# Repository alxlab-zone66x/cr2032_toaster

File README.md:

# CR2032 Toaster

This is intended to slot in vertically into a 1/2AA battery holder seen on many Macintosh computers for the PRAM battery. It will allow the use of the less expensive, easier to find and less leaky CR2032 coin batteries.

This is meant to be used laying flat in the battery holder like so:

There's also two extra through holes to solder wires for other uses.

## Bill of Materials

### v1.0 to v1.3

| Quantity | Product Number  | Datasheet                                                    |
| :------- | --------------- | ------------------------------------------------------------ |
| 1        | BAT-HLD-001-THM | [datasheet](datasheets/BAT-HLD-001-THM_Linx_Technologies.pdf) |

### v1.3b

| Quantity | Product Number  | Datasheet                                      |
| :------- | --------------- | ---------------------------------------------- |
| 1        | BAT-HLD-005-THM | [datasheet](datasheets/BAT-HLD-005-THM_TE.pdf) |

### v1.3c

| Quantity | Product Number | Datasheet                                                    |
| :------- | -------------- | ------------------------------------------------------------ |
| 1        | RK-2014        | [datasheet](datasheets/Reekart_RK-2014_1.png), [datasheet](datasheets/Reekart_RK-2014_2.png) |

### v1.3d

| Quantity | Product Number | Datasheet                                     |
| :------- | -------------- | --------------------------------------------- |
| 1        | MY-2032-08L    | [datasheet](datasheets/MYOUNG_MY-2032-08.pdf) |

## Manufacturing

The gerber, bom and component placement files are in the production folder.

The release includes the manufacturing files for JLCPCB specifically. If you need to the gerber files, BOM or component pick & place in a different format then you would have to generate them yourself.

The PCB thickness chosen should be at least 1.6mm to provide good contact with the battery holder.

## License

CR2032 Toaster by [Alexandre Marcoux](https://github.com/alxlab-zone66x/cr2032_toaster) licensed under a <a rel="license" href="http://creativecommons.org/licenses/by-nc-sa/4.0/">Creative Commons Attribution-NonCommercial-ShareAlike 4.0 International License</a>.

## Community

For more great retro hardware projects and a great community check out:

Join us in #skunkworks on [Discord](https://discord.gg/GKcvtgU7P9) to help make retro solutions available to all.

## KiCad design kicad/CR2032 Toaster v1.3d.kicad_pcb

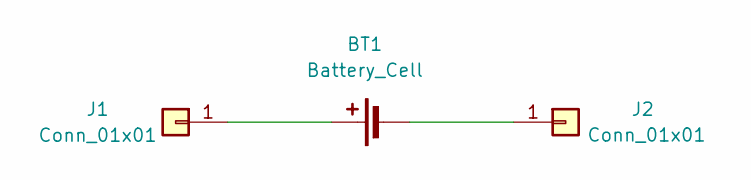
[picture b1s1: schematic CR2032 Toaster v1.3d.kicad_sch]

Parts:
BT1: Battery_Cell; BatteryHolder_MYOUNG_MY-2032-08_1x2032; LCSC C19184096
J1, J2: Conn_01x01; 6mm PTS

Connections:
unnamed: BT1.1 (+), J1.1
unnamed: BT1.2 (-), J2.1

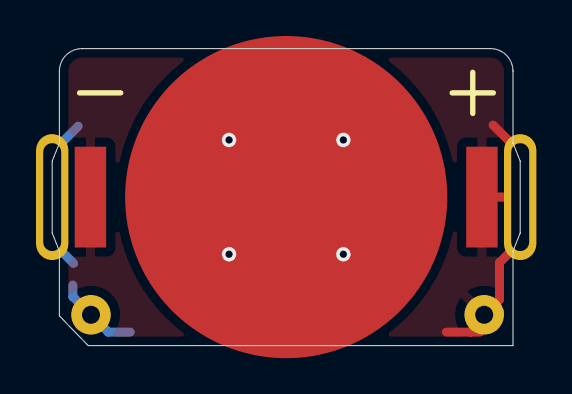
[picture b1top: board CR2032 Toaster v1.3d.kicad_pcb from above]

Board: 2 copper layers, 26.0 x 16.5 mm, 3 parts (0 on the bottom side), 2 nets.

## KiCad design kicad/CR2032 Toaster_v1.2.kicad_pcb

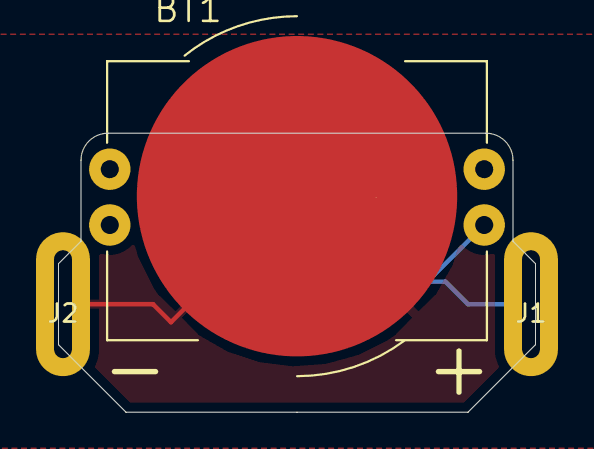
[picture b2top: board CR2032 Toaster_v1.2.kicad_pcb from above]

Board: 2 copper layers, 26.5 x 15.5 mm, 3 parts (0 on the bottom side), 2 nets.

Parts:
BT1: BAT-HLD-001-THM; BAT_BAT-HLD-001-THM
J1, J2: Conn_01x01; 6mm PTS

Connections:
unnamed: BT1.N, J2.1
unnamed: BT1.P1, BT1.P2, BT1.P3, BT1.P4, J1.1

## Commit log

2021-06-24 Version 1.2
    Improvements to the board design to help insertion into the battery holder and to hopefully increase pcb yield
2021-06-24 Update README.md
    Update Discord link.
2021-12-11 Version 1.3
2022-07-04 Update README to include manufacturing guidelines
2024-11-05 Add v1.3b for BAT-HLD-005-THM CR2032 holder
2024-11-07 Add v1.3c for RK-2014 R2032 holder
2024-11-29 Add v1.3d revision for MY-2032-08L4 SMD CR2032 holder
